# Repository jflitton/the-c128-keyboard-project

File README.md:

# the-c128-keyboard-project
This project contains designs for the plate, circuit board, and various 3d-printable bits needed to build a mechanical keyboard for the Commodore 128.

This work is very intentionally licensed for commercial use in the hope that someone will produce and sell these parts in kit and/or assembled form.  See [LICENSE.md](LICENSE.md) for more details.

## Project Goals
1. Provide a replacement keyboard for original Commodore 128 machines.  This is important because the plungers in the original Mitsumi keyboards are prone to cracking and crumbling and the external 128D(CR) keyboards are getting harder to find in reasonable condition.

2. Provide a viable option for those building a new Commodore 128 compatible machine (e.g. using the [C128 NEO](https://c128.se/))

## Configurations
While the goal is to provide fully functional, tested configurations, we're not there yet.  Here's the current status:

|Configuration|Design Complete|Tested|Notes|
|---|---|---|---|
|C128 Flat, re-using original keycaps|Yes|Yes|Fully functional
|C128 Flat, using modern keycaps|No|No|Keycaps not modeled and not commercially available|
|C128 DCR keyboard housing, re-using original keycaps|No|No|Fits in enclosure, but DCR keycaps use stabiliers not currently supported by the plate|
|C128 DCR keyboard housing, using modern keycaps|No|No|Stabiliers not currently supported by the plate.  Keycaps not modeled and not commerically available.|

## Plate design
The plate is designed to be laser cut from .060" cold rolled steel sheet (~1.5mm thick).  The [step file](plate/plate.step) is all you should need to send to a laser cutter.  The keyswitch cutouts are just a little roomier than the typical 14mm squares to accommodate powder coating, which I highly recommend.

## PCB design
The PCB is a simple 2-sided board so it should be easy enough to find a suitable manufacturer.  I used [PCBWay](https://www.pcbway.com/).  A few passives and 4 ICs are needed to make the latching keys (capslock, shift lock, and 40/80).  See [BOM.csv](pcb/bom.csv) for specific part numbers.  Note that while these parts are surface mount, I've found them large enough to hand solder even with my moderate ham-handedness.

## Printables
I've had success printing all the printable parts with a Bambu X1C wielding a .4mm nozzle with the following settings:
- .12mm layer height
- .2mm initial layer height
- 3 wall loops
- 4 top shell layers

I typically keep batches of keycap adapters small (10-12 parts per batch) to keep them consistent.  I would imagine that resin printing would be optimal in terms of quality and consistency, but that is untested.

## Keyswitches
If you're planning on reusing your stock Commodore 128 keycaps, I recommend Outemu mid-low switches, which are about 60% of full throw and keep keycap height very close to the original, despite the keycap adapters.  You'll need to print a sufficient supply of the adapters in the [printable parts](printable_parts) directory.  Alternatively, you could use full-height cherry-compatible switches and modern keycaps, though that configuration is untested for clearance and keycap height.

## Cabling
A [printable 1x25 pin cable end](printable_parts/connector_keyboard_side.stl) is included and has worked well for me.  For the Commodore 128 flat, the [motherboard side of the keyboard connector](printable_parts/connector_motherboard_side.stl) is also modeled.  This connector is an odd combination of DB25 spacing with molex kk-style pins and was not something I could source from typical suppliers.  Cabling for the 128D(CR) external keyboard has not been sorted out yet but should be feasible by simply cutting one end off a DB25 straight-through cable.

## To Do
I'd love some help from the community to accomplish the following:
- Model a Cherry-compatible set of keycaps for printing or (ideally) injection molding
- Model a compatible external enclosure: Allowing complete replacemend 128D keyboards to be built
- Design a cabling solution for 128D keyboards
- Set up a group buy for kits and/or assembled keyboards

## Authors
[Jeff Flitton](mailto:jeff@flitton.dev) - Project creator, plate and printable part designer

## Credits
[Original PCB design](https://codeberg.org/jgrip/c128-keyboard) by [Johan Grip](https://codeberg.org/jgrip/), maker of the [C128 Neo](https://c128.se/).  Minor fit adjustments and latch circuit changes were made.

## Disclaimer
This project is provided as-is, without any express or implied warranty.
By using, building, or modifying this hardware, you acknowledge that you do so at your own risk. The authors and contributors are not responsible for any damage, data loss, injury, or other consequences resulting from its use.

This project is a community-driven, open-hardware design intended for educational and hobbyist use. It is not affiliated with, endorsed by, or supported by Commodore International or any successor entities.

All trademarks, including “Commodore”, “C128”, and related names, are the property of their respective owners and are used here for descriptive and compatibility purposes only.

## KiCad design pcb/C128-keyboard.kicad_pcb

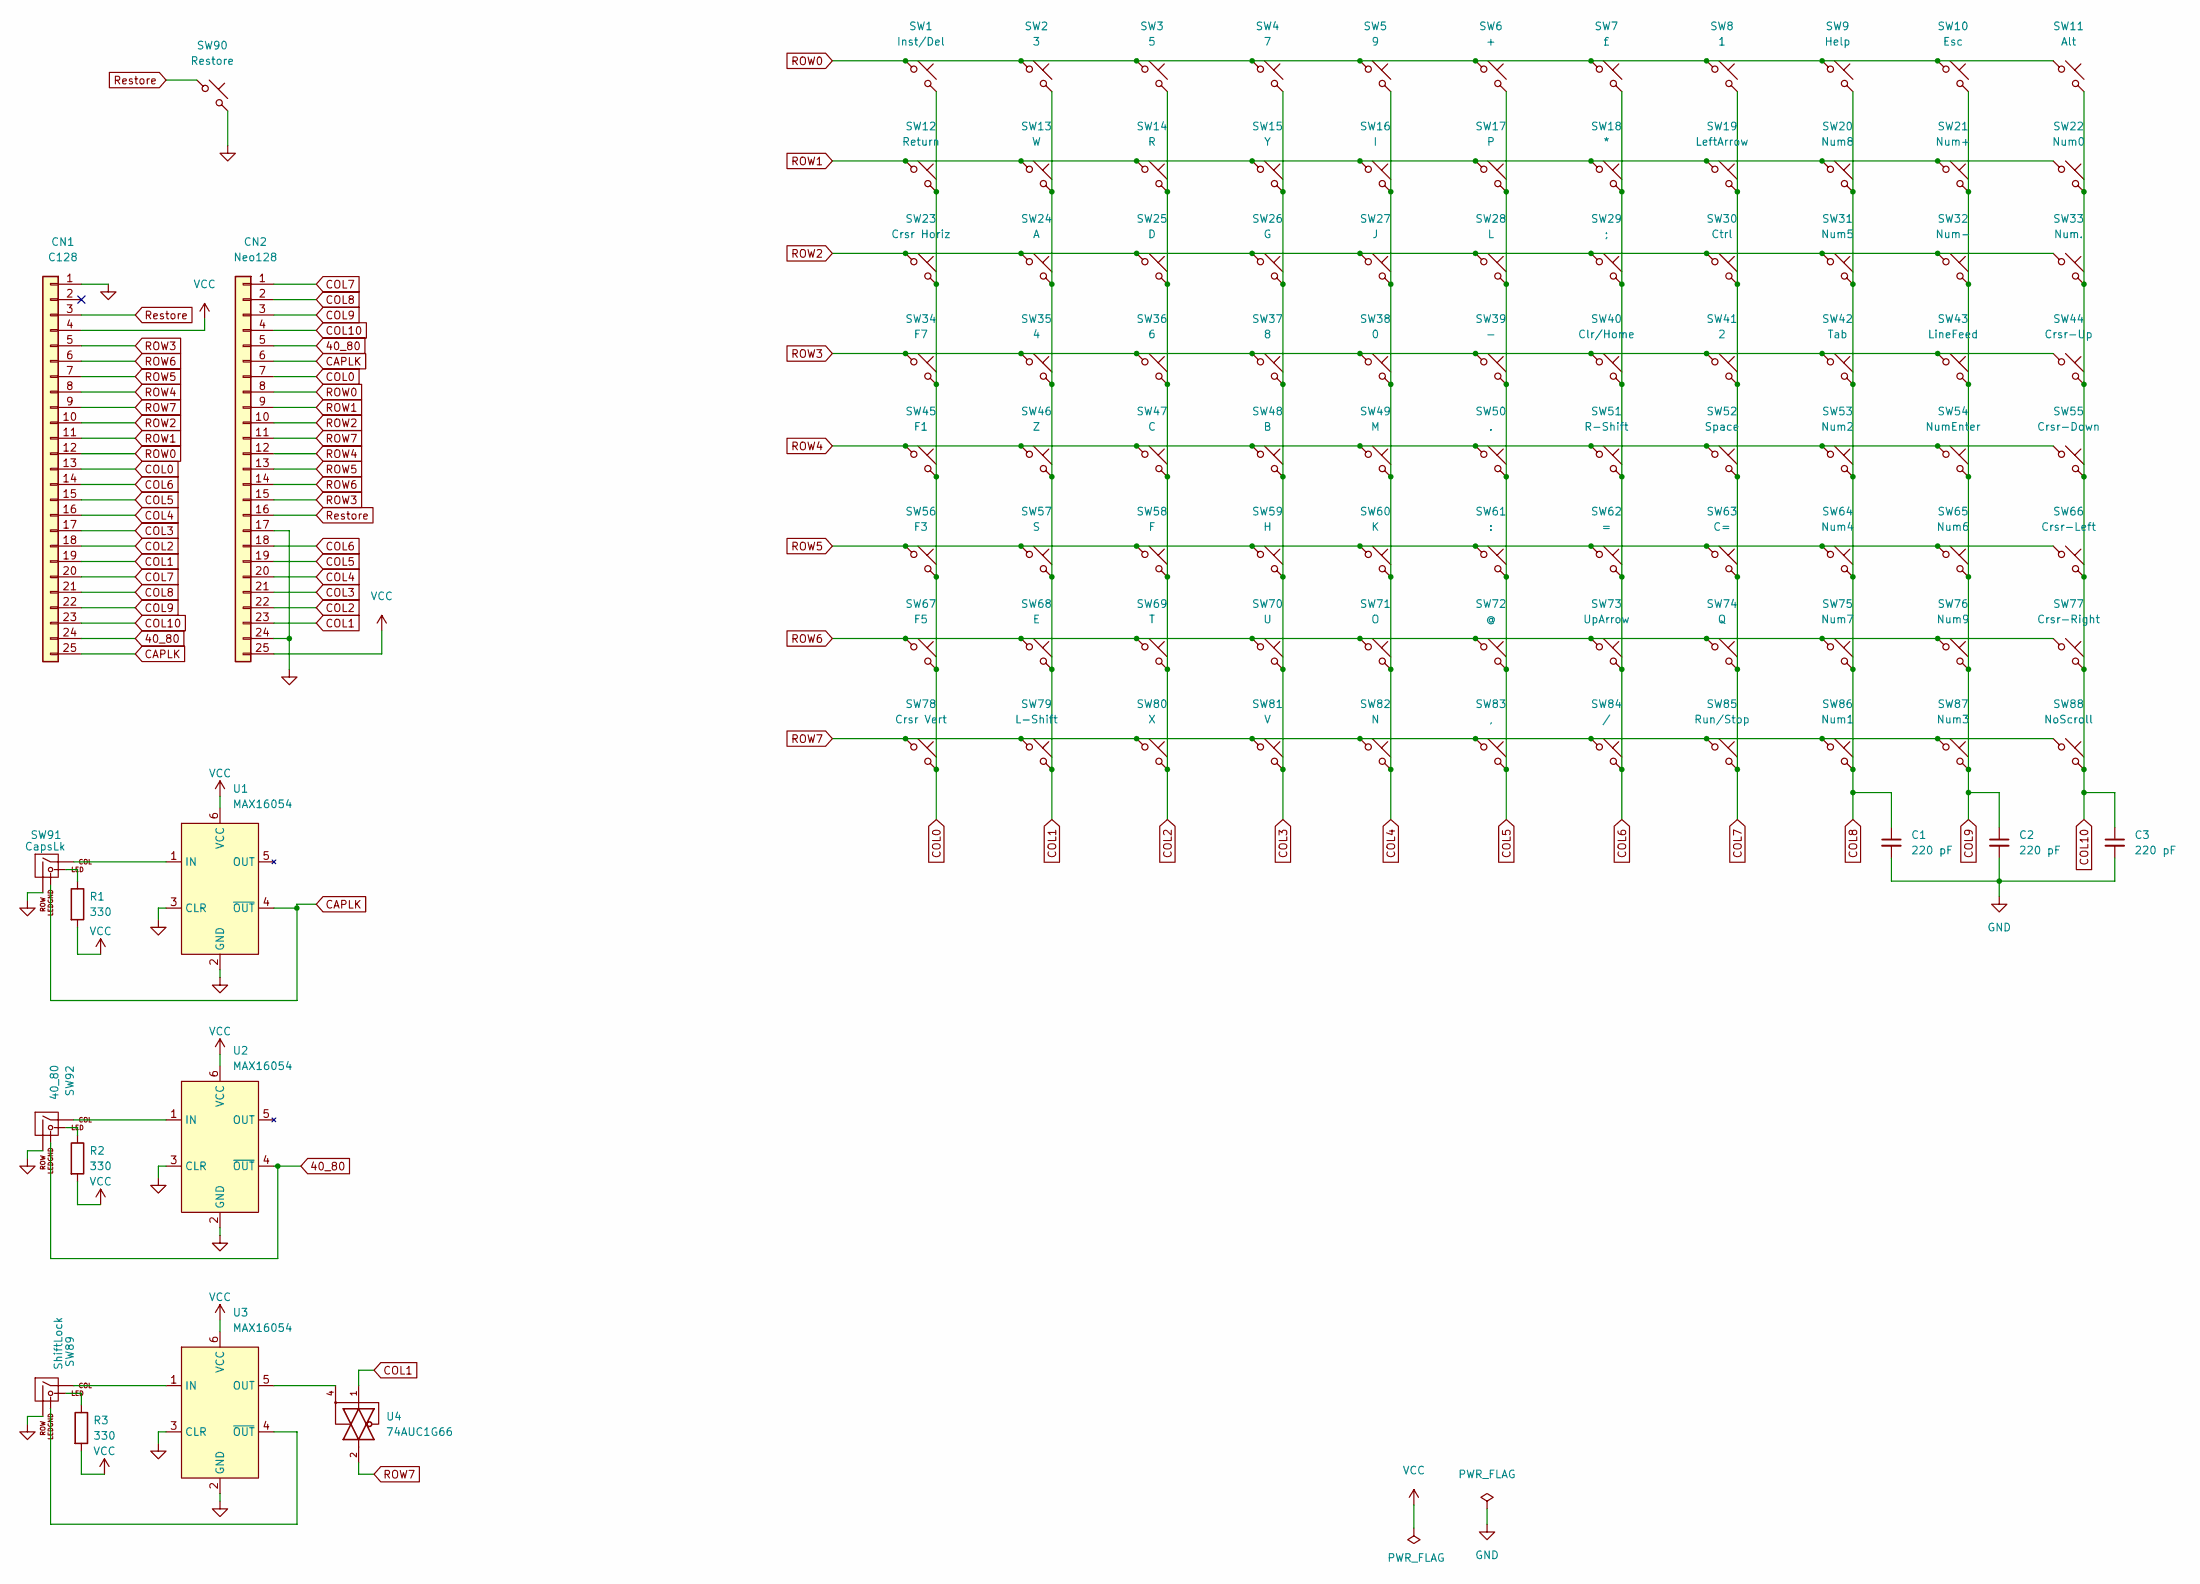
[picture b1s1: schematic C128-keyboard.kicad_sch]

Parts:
C1, C2, C3: 220 pF; C_0603_1608Metric_Pad1.08x0.95mm_HandSolder; LCSC C126556
CN1: C128
CN2: Neo128; PinHeader_1x25_P2.54mm_Vertical
R1, R2, R3: 330; R_0603_1608Metric_Pad0.98x0.95mm_HandSolder; LCSC C278617
SW1: Inst/Del; MX-1U-NoLED
SW2: 3; MX-1U-NoLED
SW3: 5; MX-1U-NoLED
SW4: 7; MX-1U-NoLED
SW5: 9; MX-1U-NoLED
SW6: +; MX-1U-NoLED
SW7: £; MX-1U-NoLED
SW8: 1; MX-1U-NoLED
SW9: Help; MX-1U-NoLED
SW10: Esc; MX-1U-NoLED
SW11: Alt; MX-1U-NoLED
SW12: Return; MX-2U-NoLED
SW13: W; MX-1U-NoLED
SW14: R; MX-1U-NoLED
SW15: Y; MX-1U-NoLED
SW16: I; MX-1U-NoLED
SW17: P; MX-1U-NoLED
SW18: *; MX-1U-NoLED
SW19: LeftArrow; MX-1U-NoLED
SW20: Num8; MX-1U-NoLED
SW21: Num+; MX-1U-NoLED
SW22: Num0; MX-2U-NoLED
SW23: Crsr Horiz; MX-1U-NoLED
SW24: A; MX-1U-NoLED
SW25: D; MX-1U-NoLED
SW26: G; MX-1U-NoLED
SW27: J; MX-1U-NoLED
SW28: L; MX-1U-NoLED
SW29: ;; MX-1U-NoLED
SW30: Ctrl; MX-1U-NoLED
SW31: Num5; MX-1U-NoLED
SW32: Num-; MX-1U-NoLED
SW33: Num.; MX-1U-NoLED
SW34: F7; MX-1U-NoLED
SW35: 4; MX-1U-NoLED
SW36: 6; MX-1U-NoLED
SW37: 8; MX-1U-NoLED
SW38: 0; MX-1U-NoLED
SW39: -; MX-1U-NoLED
SW40: Clr/Home; MX-1U-NoLED
SW41: 2; MX-1U-NoLED
SW42: Tab; MX-1U-NoLED
SW43: LineFeed; MX-1U-NoLED
SW44: Crsr-Up; MX-1U-NoLED
SW45: F1; MX-1U-NoLED
SW46: Z; MX-1U-NoLED
SW47: C; MX-1U-NoLED
SW48: B; MX-1U-NoLED
SW49: M; MX-1U-NoLED
SW50: .; MX-1U-NoLED
SW51: R-Shift; MX-1U-NoLED
SW52: Space; MX-7_9U-ReversedStabilizers-NoLED
SW53: Num2; MX-1U-NoLED
SW54: NumEnter; MX-2U-FLIPPED
SW55: Crsr-Down; MX-1U-NoLED
SW56: F3; MX-1U-NoLED
SW57: S; MX-1U-NoLED
SW58: F; MX-1U-NoLED
SW59: H; MX-1U-NoLED
SW60: K; MX-1U-NoLED
SW61: :; MX-1U-NoLED
SW62: =; MX-1U-NoLED
SW63: C=; MX-1U-NoLED
SW64: Num4; MX-1U-NoLED
SW65: Num6; MX-1U-NoLED
SW66: Crsr-Left; MX-1U-NoLED
SW67: F5; MX-1U-NoLED
SW68: E; MX-1U-NoLED
SW69: T; MX-1U-NoLED
SW70: U; MX-1U-NoLED
SW71: O; MX-1U-NoLED
SW72: @; MX-1U-NoLED
SW73: UpArrow; MX-1U-NoLED
SW74: Q; MX-1U-NoLED
SW75: Num7; MX-1U-NoLED
SW76: Num9; MX-1U-NoLED
SW77: Crsr-Right; MX-1U-NoLED
SW78: Crsr Vert; MX-1U-NoLED
SW79: L-Shift; MX-1.5U-NoLED
SW80: X; MX-1U-NoLED
SW81: V; MX-1U-NoLED
SW82: N; MX-1U-NoLED
SW83: ,; MX-1U-NoLED
SW84: /; MX-1U-NoLED
SW85: Run/Stop; MX-1U-NoLED
SW86: Num1; MX-1U-NoLED
SW87: Num3; MX-1U-NoLED
SW88: NoScroll; MX-1U-NoLED
SW89: ShiftLock; MX-1U
SW90: Restore; MX-1.5U-NoLED
SW91: CapsLk; MX-1U
SW92: 40_80; MX-1U
U1, U2, U3: MAX16054; TSOT-23-6
U4: 74AUC1G66; TSOP-5_1.65x3.05mm_P0.95mm; LCSC C327492

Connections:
40_80: CN1.24, CN2.5, SW92.4 (LEDGND), U2.4 (~OUT)
CAPLK: CN1.25, CN2.6, SW91.4 (LEDGND), U1.4 (~OUT)
COL0: CN1.13, CN2.7, SW1.2, SW12.2, SW23.2, SW34.2, SW45.2, SW56.2, SW67.2, SW78.2
COL1: CN1.19, CN2.23, SW2.2, SW13.2, SW24.2, SW35.2, SW46.2, SW57.2, SW68.2, SW79.2, U4.1
COL2: CN1.18, CN2.22, SW3.2, SW14.2, SW25.2, SW36.2, SW47.2, SW58.2, SW69.2, SW80.2
COL3: CN1.17, CN2.21, SW4.2, SW15.2, SW26.2, SW37.2, SW48.2, SW59.2, SW70.2, SW81.2
COL4: CN1.16, CN2.20, SW5.2, SW16.2, SW27.2, SW38.2, SW49.2, SW60.2, SW71.2, SW82.2
COL5: CN1.15, CN2.19, SW6.2, SW17.2, SW28.2, SW39.2, SW50.2, SW61.2, SW72.2, SW83.2
COL6: CN1.14, CN2.18, SW7.2, SW18.2, SW29.2, SW40.2, SW51.2, SW62.2, SW73.2, SW84.2
COL7: CN1.20, CN2.1, SW8.2, SW19.2, SW30.2, SW41.2, SW52.2, SW63.2, SW74.2, SW85.2
COL8: C1.1, CN1.21, CN2.2, SW9.2, SW20.2, SW31.2, SW42.2, SW53.2, SW64.2, SW75.2, SW86.2
COL9: C2.1, CN1.22, CN2.3, SW10.2, SW21.2, SW32.2, SW43.2, SW54.2, SW65.2, SW76.2, SW87.2
COL10: C3.1, CN1.23, CN2.4, SW11.2, SW22.2, SW33.2, SW44.2, SW55.2, SW66.2, SW77.2, SW88.2
GND: C1.2, C2.2, C3.2, CN1.1, CN2.17, CN2.24, SW89.2 (ROW), SW90.2, SW91.2 (ROW), SW92.2 (ROW), U1.2 (GND), U1.3 (CLR), U2.2 (GND), U2.3 (CLR), U3.2 (GND), U3.3 (CLR), U4.3 (GND)
unnamed: R1.1, SW91.3 (LED)
unnamed: R2.1, SW92.3 (LED)
unnamed: R3.1, SW89.3 (LED)
unnamed: SW89.1 (COL), U3.1 (IN)
unnamed: SW89.4 (LEDGND), U3.4 (~OUT)
unnamed: SW91.1 (COL), U1.1 (IN)
unnamed: SW92.1 (COL), U2.1 (IN)
unnamed: U3.5 (OUT), U4.4
ROW0: CN1.12, CN2.8, SW1.1, SW2.1, SW3.1, SW4.1, SW5.1, SW6.1, SW7.1, SW8.1, SW9.1, SW10.1, SW11.1
ROW1: CN1.11, CN2.9, SW12.1, SW13.1, SW14.1, SW15.1, SW16.1, SW17.1, SW18.1, SW19.1, SW20.1, SW21.1, SW22.1
ROW2: CN1.10, CN2.10, SW23.1, SW24.1, SW25.1, SW26.1, SW27.1, SW28.1, SW29.1, SW30.1, SW31.1, SW32.1, SW33.1
ROW3: CN1.5, CN2.15, SW34.1, SW35.1, SW36.1, SW37.1, SW38.1, SW39.1, SW40.1, SW41.1, SW42.1, SW43.1, SW44.1
ROW4: CN1.8, CN2.12, SW45.1, SW46.1, SW47.1, SW48.1, SW49.1, SW50.1, SW51.1, SW52.1, SW53.1, SW54.1, SW55.1
ROW5: CN1.7, CN2.13, SW56.1, SW57.1, SW58.1, SW59.1, SW60.1, SW61.1, SW62.1, SW63.1, SW64.1, SW65.1, SW66.1
ROW6: CN1.6, CN2.14, SW67.1, SW68.1, SW69.1, SW70.1, SW71.1, SW72.1, SW73.1, SW74.1, SW75.1, SW76.1, SW77.1
ROW7: CN1.9, CN2.11, SW78.1, SW79.1, SW80.1, SW81.1, SW82.1, SW83.1, SW84.1, SW85.1, SW86.1, SW87.1, SW88.1, U4.2
Restore: CN1.3, CN2.16, SW90.1
VCC: CN1.4, CN2.25, R1.2, R2.2, R3.2, U1.6 (VCC), U2.6 (VCC), U3.6 (VCC), U4.5 (VCC)

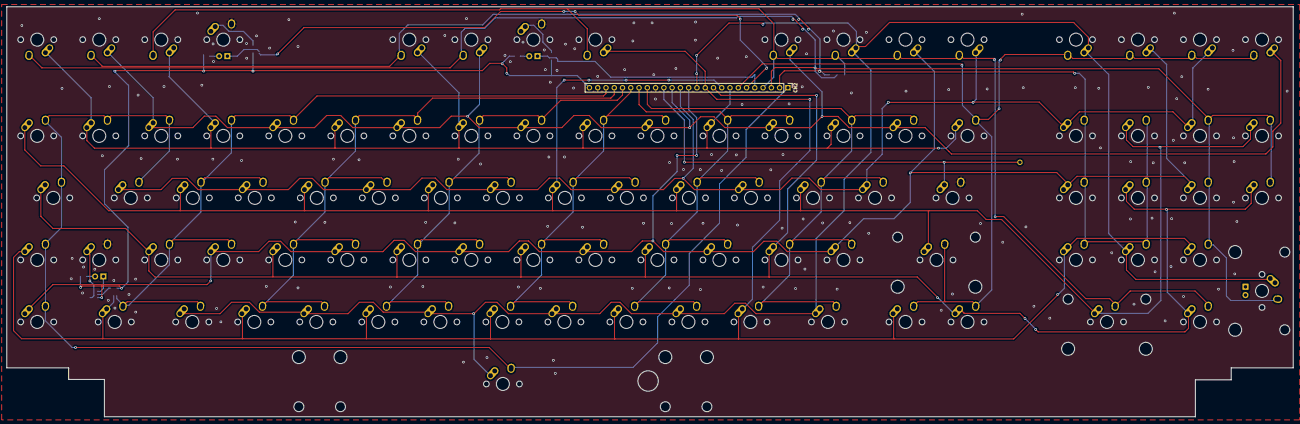
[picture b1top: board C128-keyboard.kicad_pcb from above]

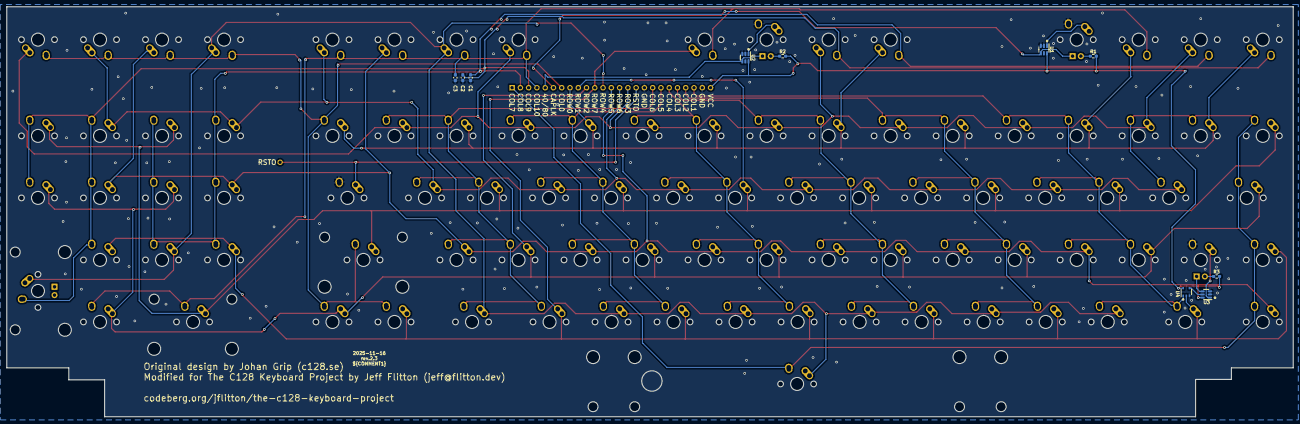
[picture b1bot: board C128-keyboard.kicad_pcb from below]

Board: 2 copper layers, 395.2 x 125.9 mm, 103 parts (10 on the bottom side), 32 nets.

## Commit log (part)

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2025-10-11 Initial import of PCB
2025-10-11 Cleanup
2025-10-14 Wiring fixes for latch keys
2025-10-14 Plate v1.2
2025-10-14 Adding printables
2025-10-14 Adding pad for plate grounding strap
2025-10-14 CN2 labels and attribution
2025-10-15 ignore
2025-10-17 Moving stabilizers to align with c128 original spacebar
2025-10-18 Stabilizer mounts aligned to stock C128 spacing
2025-10-18 PCB 2.2 with extra restore pin
2025-10-20 Edge cut cleanup
2025-11-01 README updates
2025-11-01 More README updates
2025-11-09 New plate model with params
2025-11-09 moar printables
2025-11-09 Minor plate fitment adjustments and shorter mb-side connector
2025-11-10 Disclaimer
2025-11-14 Adding pin 1 indicators for ICs, no functional changes
2025-11-16 Updating for 128DCR external enclosure
2025-11-17 Improved spacebar adapter
2025-11-17 Adding configurations based on latest testing
2025-11-17 Adjusting thickness
2025-11-24 128D spacebar stab adapter
2026-02-22 Adding BOM
2026-02-22 Fixing BOM
2026-02-22 New BOM
